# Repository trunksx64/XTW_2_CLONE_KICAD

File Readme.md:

# XTW2 Clone ::: Revisión R1 :: Versión 1.2.1

## Razón de Ser e Inspiración

Este pequeño stick se diseñó como una prueba de aprendizaje para el uso de los microcontroladores STM32 y además por error al tratar de leer la memoria de un programador XTW2, este quedo inutilizable.
originalmente este programador de memorias salió dañado, presentando muchos errores principalmente en la lectura de Memorias Eeproms, se tomó la iniciativa de crear un software tanto para el STM32 y una GUI para Linux.
Aún están en desarrollo por mi parte, falta de tiempo en realidad, se espera en un futuro terminarlo.

## Características del Hardware

  * Microcontrolador STM32F103C8T6.
  * Base ZIF de 16pines, similar de la Marca 3M.
  * Puerto USB 2.0 Macho tipo A.
  * Pinhead de 5 pines para Programamcion y Debug ST-LINK.
  * Testpoint para Puerto UART Basico.
  * Boton de Reset.

## Características Específicas

Se tomó un tamaño similar al Original, agregando algunos componentes para usarlo en Debug mediante STM32CubeIDE, distribuyendo un poco mejor los componentes y usando tamaños más comerciales como sencillos de soldar.

## Microcontrolador

* Architecture 32-bit.
* STM32F103C8T6:

	* ARM®32-bit Cortex®-M3 CPU Core 
		* 72 MHz maximum frequency,1.25 DMIPS/MHz (Dhrystone 2.1) performance at 0 wait state memory access
		* Single-cycle multiplication and hardware division
	
	* Memories 
		* 64 or 128 Kbytes of Flash memory
	*	 20 Kbytes of SRAM
	
	* Clock, reset and supply management 
		* 2.0 to 3.6 V application supply and I/Os
		* POR, PDR, and programmable voltage detector (PVD)
		* 4-to-16 MHz crystal oscillator
		* Internal 8 MHz factory-trimmed RC
		* Internal 40 kHz RC
		* PLL for CPU clock
		* 32 kHz oscillator for RTC with calibration

	* Low-power 
		* Sleep, Stop and Standby modes
		* VBAT supply for RTC and backup registers
	
	* 2 x 12-bit, 1 μs A/D converters (up to 16 channels) 
		* Conversion range: 0 to 3.6 V
		* Dual-sample and hold capability
		* Temperature sensor
	
	* DMA 
		* 7-channel DMA controller
		* Peripherals supported: timers, ADC, SPIs, I2Cs and USARTs
	
	* Up to 80 fast I/O ports 
		* 26/37/51/80 I/Os, all mappable on 16 external interrupt vectors and almost all 5 V-tolerant
		* Debug mode 
		* Serial wire debug (SWD) & JTAG interfaces
	
	* 7 timers 
		* Three 16-bit timers, each with up to 4 IC/OC/PWM or pulse counter and quadrature (incremental) encoder input
		* 16-bit, motor control PWM timer with dead-time generation and emergency stop
		* 2 watchdog timers (Independent and Window)
		* SysTick timer 24-bit downcounter
	
	* Up to 9 communication interfaces 
		* Up to 2 x I2C interfaces (SMBus/PMBus)
		* Up to 3 USARTs (ISO 7816 interface, LIN, IrDA capability, modem control)
		* Up to 2 SPIs (18 Mbit/s)
		* CAN interface (2.0B Active)
		* USB 2.0 full-speed interface
	
	* CRC calculation unit, 96-bit unique ID 
	* Packages are ECOPACK® 

## Versiones

* 2023 : 1.0.0 : Primera Versión, KiCAD V7 es requerido.
* 2023 : 1.0.0 : Diseño de Liberias para Modelo 3D del Socket ZIF.
* 2023 : 1.2.0 : Se Agrego Boton de Reset, Pin SWO para Debug, Dos Testpoint para UART.
* 2023 : 1.2.1 : Se Corrigieron algunos Errores y se agrego un Segundo LED de Busy.

## ERRATAS

* Ninguna en el Momento.

## Créditos

xDNA Electronics & Desing es una microempresa Personal, que se dedica y encarga de elaborar proyectos de Control y Automatización por pedido, su idea es colaborar y ayudar a quines a si lo requieran, el proyecto se hizo principalmente como Hobby el cual gracias a terceros se pudo implementar y hacer su creación, por lo cual se da la libertad de usarlo para experimentar sin hacer uso comercial del mismo.

## Licencia

Licensed under Attribution-NonCommercial-ShareAlike 4.0 International (CC BY-NC-SA 4.0)

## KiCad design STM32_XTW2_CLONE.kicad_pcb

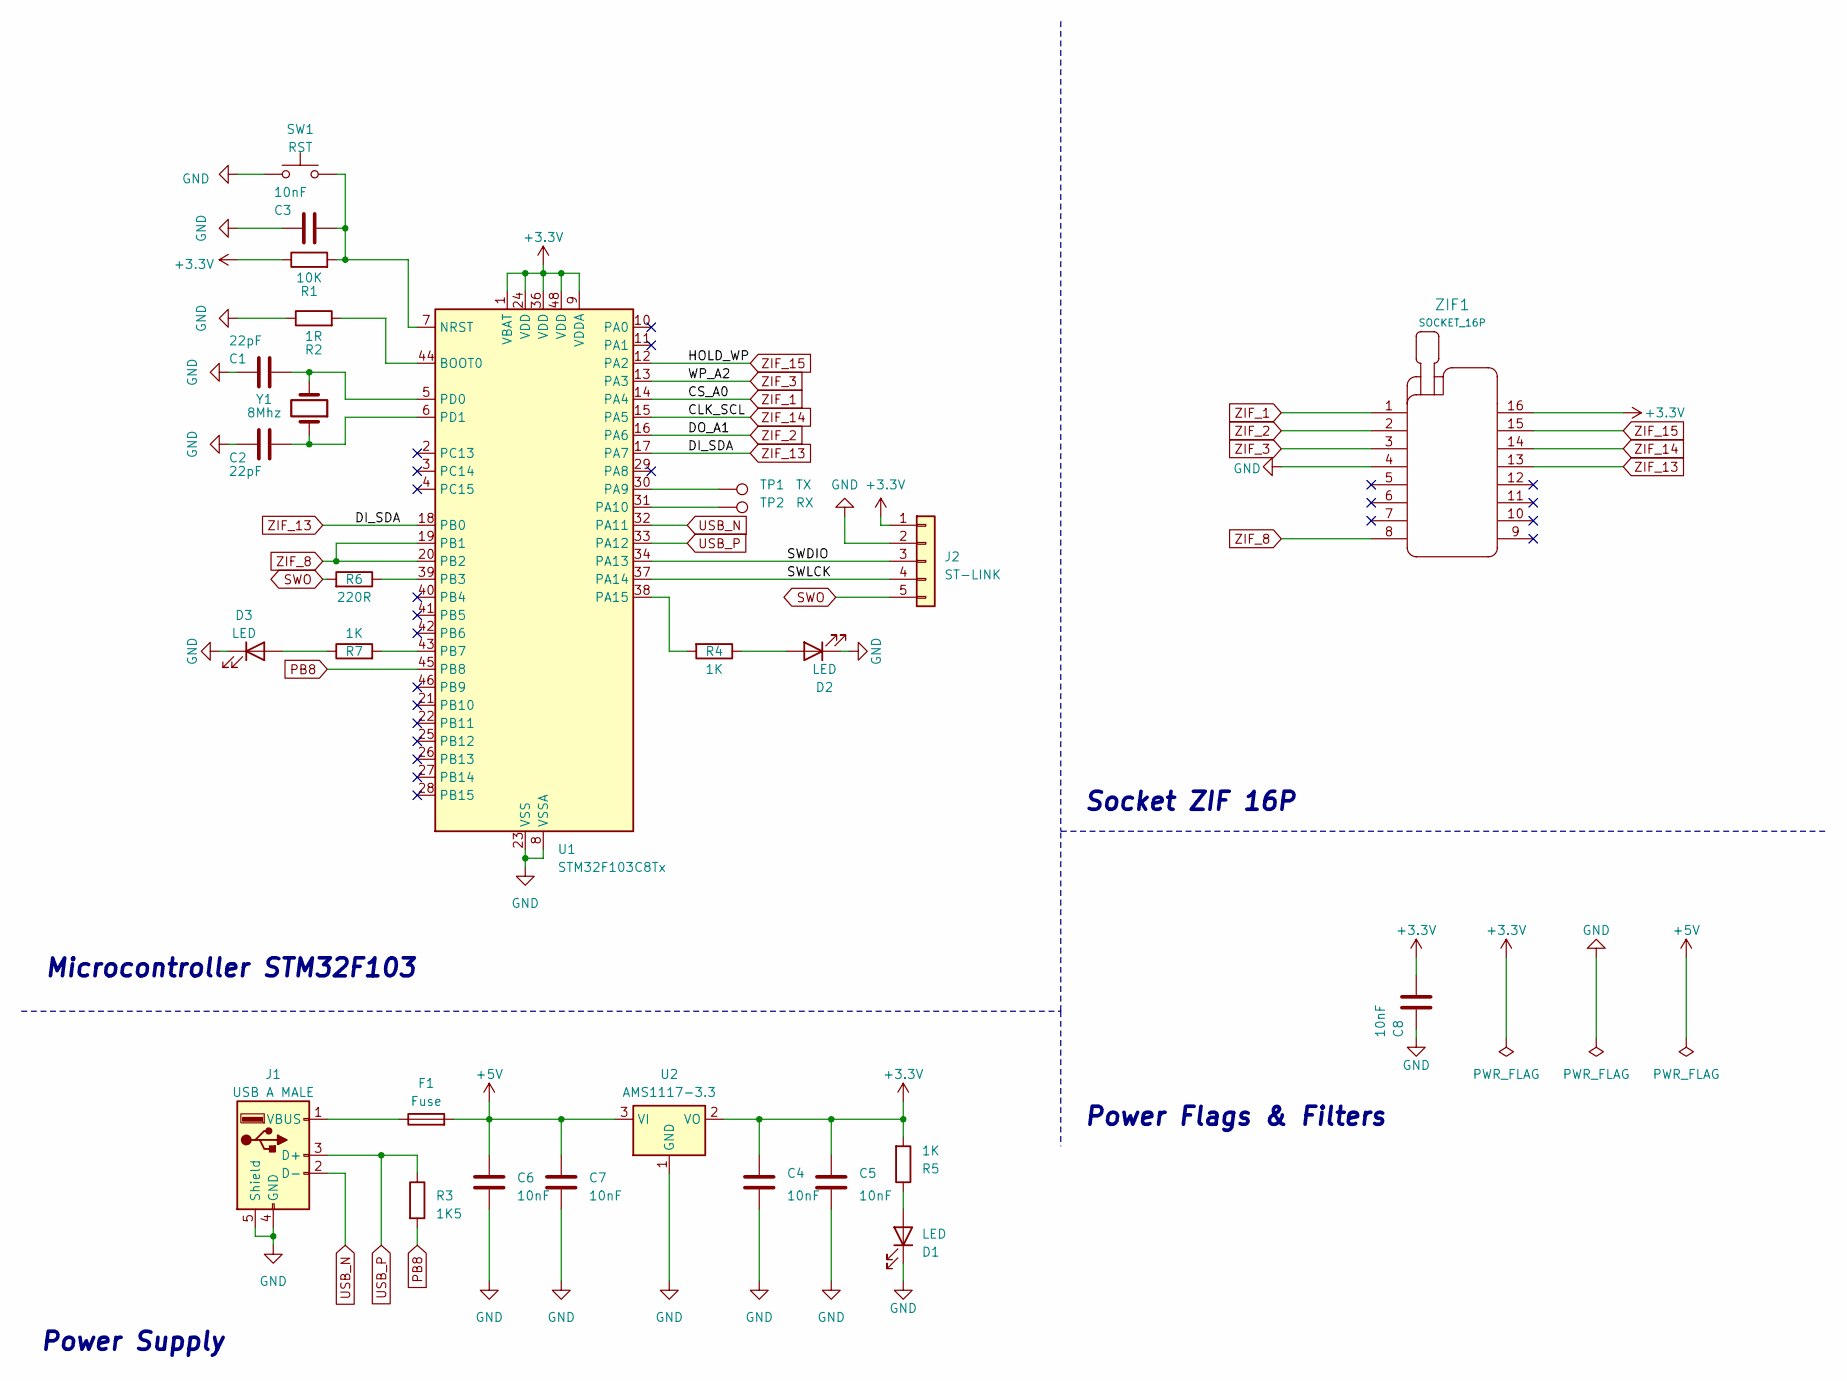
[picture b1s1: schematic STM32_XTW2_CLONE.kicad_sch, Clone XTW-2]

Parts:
C1, C2: 22pF; C_1206_3216Metric
C3, C4, C5, C6, C7, C8: 10nF; C_1206_3216Metric
D1, D2, D3: LED; LED_1206_3216Metric
F1: Fuse; Fuse_1206_3216Metric
J1: USB A MALE; USB_A_LP_C_ASSMANN
J2: ST-LINK; PinHeader_1x05_P2.54mm_Vertical
R1: 10K; R_1206_3216Metric
R2: 1R; R_1206_3216Metric
R3: 1K5; R_1206_3216Metric
R4, R5, R7: 1K; R_1206_3216Metric
R6: 220R; R_1206_3216Metric
SW1: RST; TACT_SWITCH_6x3.5mm
TP1: TX; TestPoint_Pad_D1.0mm
TP2: RX; TestPoint_Pad_D1.0mm
U1: STM32F103C8Tx; LQFP-48_7x7mm_P0.5mm
U2: AMS1117-3.3; SOT-223-3_TabPin2
Y1: 8Mhz; Crystal_SMD_HC49-SD
ZIF1: SOCKET_16P; SOCKET_16P_W35.2_H14.9_P7.62x2.54

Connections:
+3.3V: C4.1, C5.1, C8.1, J2.1, R1.1, R5.2, U1.1 (VBAT), U1.9 (VDDA), U1.24 (VDD), U1.36 (VDD), U1.48 (VDD), U2.2 (VO), ZIF1.16; also elsewhere on the board
+5V: C6.1, C7.1, F1.2, U2.3 (VI)
/SWDIO: J2.3, U1.34 (PA13)
/SWLCK: J2.4, U1.37 (PA14)
GND: C1.2, C2.2, C3.2, C4.2, C5.2, C6.2, C7.2, C8.2, D1.1 (K), D2.1 (K), D3.1 (K), J1.4 (GND), J1.5 (Shield), J2.2, R2.1, SW1.2, U1.8 (VSSA), U1.23 (VSS), U1.35 (VSS), U1.47 (VSS), U2.1 (GND), ZIF1.4; also elsewhere on the board
unnamed: D1.2 (A), R5.1
unnamed: D2.2 (A), R4.1
unnamed: D3.2 (A), R7.1
unnamed: F1.1, J1.1 (VBUS)
unnamed: R2.2, U1.44 (BOOT0)
unnamed: C3.1, R1.2, SW1.1, U1.7 (NRST)
unnamed: TP1.1, U1.30 (PA9)
unnamed: TP2.1, U1.31 (PA10)
unnamed: R4.2, U1.38 (PA15)
unnamed: R6.1, U1.39 (PB3)
unnamed: R7.2, U1.43 (PB7)
unnamed: C1.1, U1.5 (PD0), Y1.2
unnamed: C2.1, U1.6 (PD1), Y1.1
PB8: R3.2, U1.45 (PB8)
SWO: J2.5, R6.2
USB_N: J1.2 (D-), U1.32 (PA11)
USB_P: J1.3 (D+), R3.1, U1.33 (PA12)
ZIF_1: U1.14 (PA4), ZIF1.1; also elsewhere on the board
ZIF_2: U1.16 (PA6), ZIF1.2; also elsewhere on the board
ZIF_3: U1.13 (PA3), ZIF1.3; also elsewhere on the board
ZIF_8: U1.19 (PB1), U1.20 (PB2), ZIF1.8; also elsewhere on the board
ZIF_13: U1.17 (PA7), U1.18 (PB0), ZIF1.13; also elsewhere on the board
ZIF_14: U1.15 (PA5), ZIF1.14; also elsewhere on the board
ZIF_15: U1.12 (PA2), ZIF1.15; also elsewhere on the board

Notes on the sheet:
Power Supply
Microcontroller STM32F103
Socket ZIF 16P
Power Flags & Filters

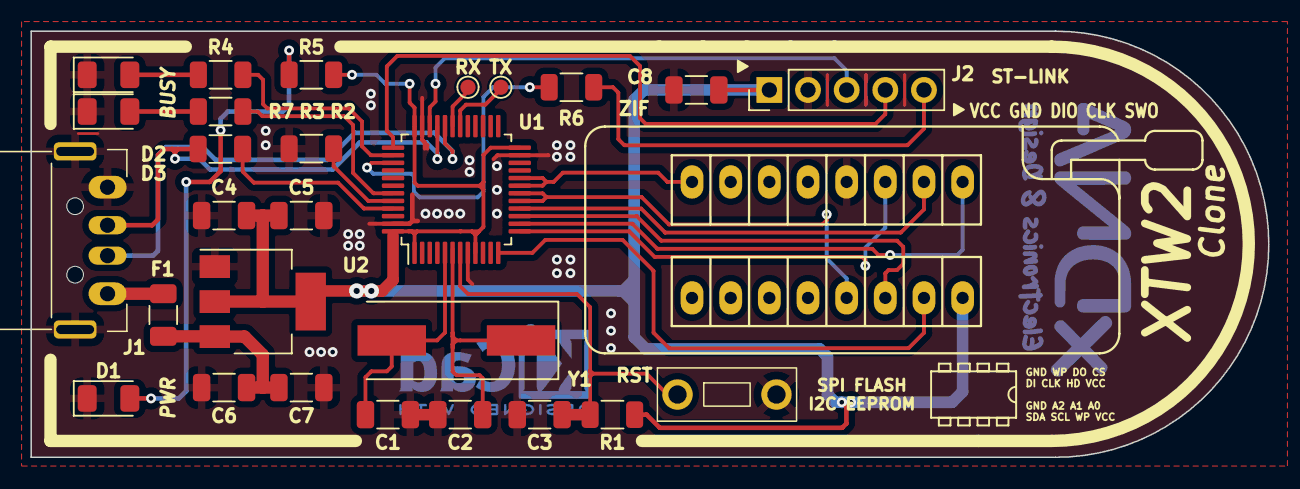
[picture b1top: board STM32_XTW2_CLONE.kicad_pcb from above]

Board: 2 copper layers, 81.3 x 28.0 mm, 29 parts (1 on the bottom side), 29 nets.

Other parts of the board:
Ge: LOGO; symbol_commons_by_nc_nd_skill_small
ZIF: SOCKET_16P; SOCKET_16P_W35.2_H14.9_P7.62x2.54

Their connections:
+3.3V: ZIF.16; also elsewhere on the board
GND: ZIF.4; also elsewhere on the board
ZIF_1: ZIF.1; also elsewhere on the board
ZIF_2: ZIF.2; also elsewhere on the board
ZIF_3: ZIF.3; also elsewhere on the board
ZIF_8: ZIF.8; also elsewhere on the board
ZIF_13: ZIF.13; also elsewhere on the board
ZIF_14: ZIF.14; also elsewhere on the board
ZIF_15: ZIF.15; also elsewhere on the board

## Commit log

2023-03-25 24/03/23/A
2023-03-25 24/03/23/B
2023-03-25 24/03/23/C
2023-03-25 25/03/23/C
2023-03-25 25/03/23/D
2023-12-26 26/12/13/A
